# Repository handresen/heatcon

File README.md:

# HeatCon
Simple controller for water based floor heating.
The project was initiated when the old controller for the floor heating in our house broke down. I wanted the ability to control floor heating remotely from mobile and web. A prototype has been up and running for six weeks now without any problems.

## Summary
* Solid state switches (mosfets)
* Optocouplers to isolate MCU from 24V
* ESP8266 socket (WeMos D1 mini)
* Integrated switching power 24V-3.3V, single power for MCU and actuators
* No moving parts (ie no magnetic relays)
* EPS8266 powers opto couplers, mosfets drive the actuators
* Optionally separate ground and power for MCU and actuators
* Should work well for other actuators 6V-30V, up to 2.5A/channel (limited by PCB trace widths, more with thicker Cu)

## Schema

## Layout

## Model

## PCB
PCB by https://jlcpcb.com/, ENIG with black solder mask
<br/><br/>

<br/>

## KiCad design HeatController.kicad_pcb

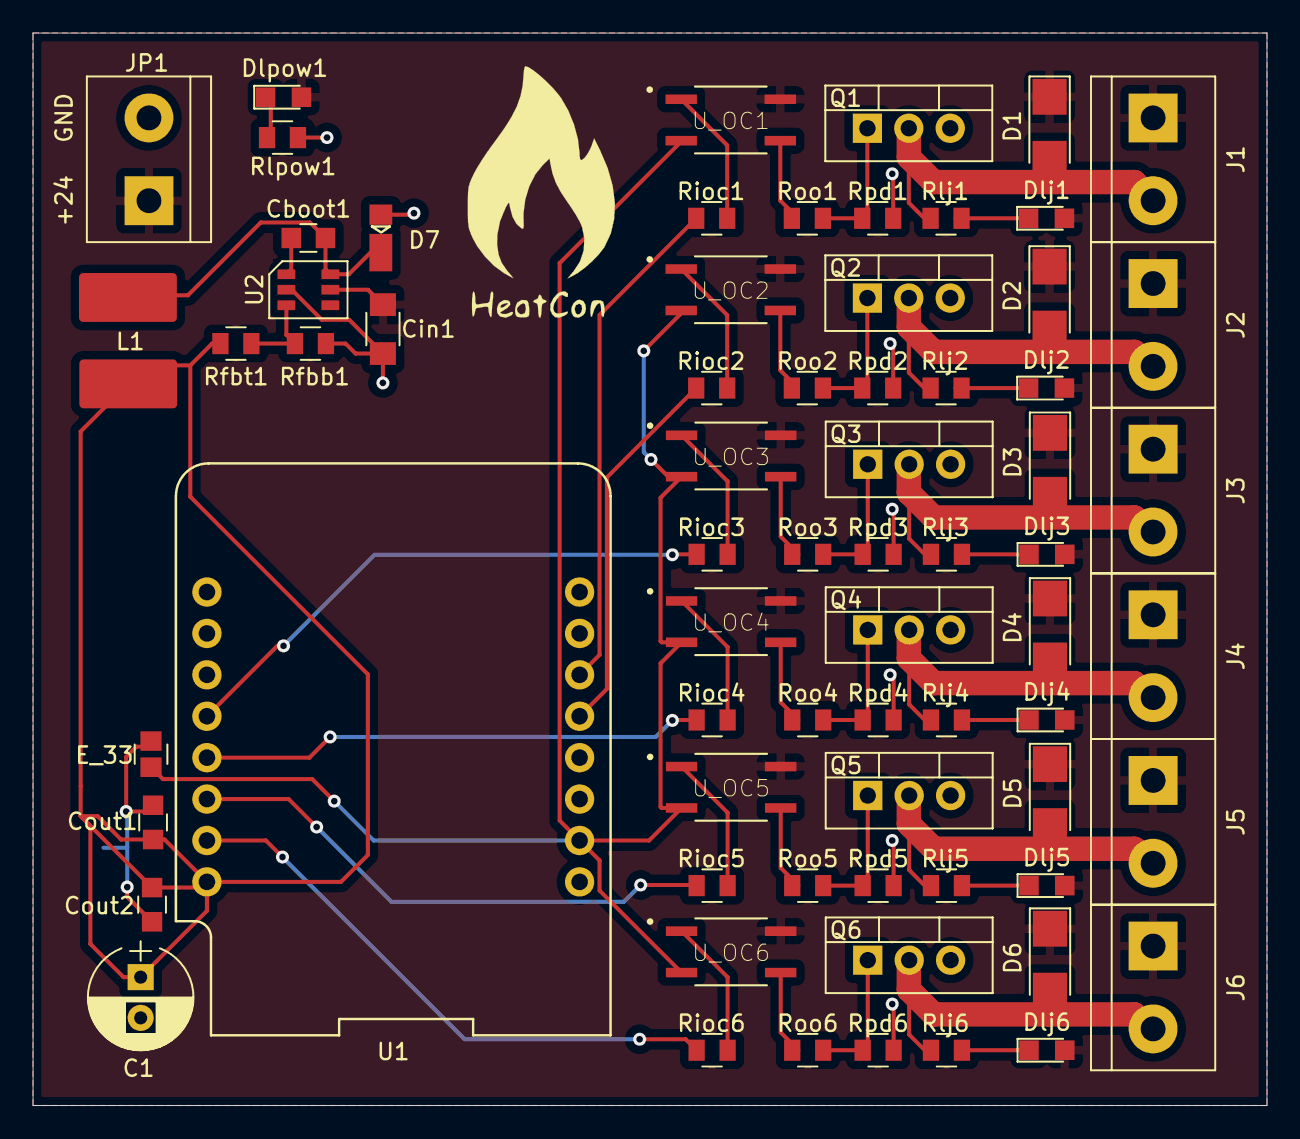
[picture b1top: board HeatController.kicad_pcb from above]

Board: 2 copper layers, 75.7 x 65.8 mm, 69 parts (0 on the bottom side), 44 nets.

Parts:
C1: 100uF; CP_Radial_D6.3mm_P2.50mm
Cboot1: 100nF; C_0805_H
Cin1: 4.7uF; C_1206
Cout1, Cout2: 22uF; C_0805_H
D1, D2, D3, D4, D5, D6: 1N4007; DO-214AC
D7: 600mV; SOD-123EP
Dlj1, Dlj2, Dlj3, Dlj4, Dlj5, Dlj6: LED; LED_0805
Dlpow1: LED; LED_0805
E_33: 0; R_0805_SHORT
J1, J2, J3, J4, J5, J6: Screw_Terminal_01x02; TerminalBlock_bornier-2_P5.08mm_tight
JP1: Screw_Terminal_01x02; TerminalBlock_bornier-2_P5.08mm_tight
L1: 15uH; SRN_INDUCTOR
Q1, Q2, Q3, Q4, Q5, Q6: IRF3205; TO-220-3_Vertical
Rfbb1: R; R_0805_H
Rfbt1: 64.9k; R_0805_H
Rioc1, Rioc2, Rioc3, Rioc4, Rioc5, Rioc6: 400; R_0805_H
Rlj1, Rlj2, Rlj3, Rlj4, Rlj5, Rlj6: 7k; R_0805_H
Rlpow1: 7k; R_0805_H
Roo1, Roo2, Roo3, Roo4, Roo5, Roo6: 20k; R_0805_H
Rpd1, Rpd2, Rpd3, Rpd4, Rpd5, Rpd6: 20k; R_0805_H
U1: WeMos_D1_mini; wemos-d1-mini-with-pin-header
U2: LMR14010ADDC; LRM14010A
U_OC1, U_OC2, U_OC3, U_OC4, U_OC5, U_OC6: EL357N(A)(TA)-G; SOP254P700X200-4N

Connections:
/3V3: C1.1, Cout1.1, Cout2.1, L1.1, Rfbt1.1, U1.8
/24V: Cin1.1, D1.1, D2.1, D3.1, D4.1, D5.1, D6.1, Dlj1.2, Dlj2.2, Dlj3.2, Dlj4.2, Dlj5.2, Dlj6.2, Dlpow1.2, J1.1, J2.1, J3.1, J4.1, J5.1, J6.1, JP1.1, U2.5, U_OC1.4, U_OC2.4, U_OC3.4, U_OC4.4, U_OC5.4, U_OC6.4
/D1: Rioc1.2, U1.14
/D2: Rioc2.2, U1.13
/D5: Rioc3.2, U1.4
/D6: Rioc4.2, U1.5
/D7: Rioc5.2, U1.6
/D8: Rioc6.2, U1.7
/GND2: E_33.1, U1.10, U_OC1.2, U_OC2.2, U_OC3.2, U_OC4.2, U_OC5.2, U_OC6.2
/SW: Cboot1.2, D7.1, L1.2, U2.6
GND: C1.2, Cin1.2, Cout1.2, Cout2.2, D7.2, E_33.2, JP1.2, Q1.3, Q2.3, Q3.3, Q4.3, Q5.3, Q6.3, Rfbb1.2, Rlpow1.1, Rpd1.2, Rpd2.2, Rpd3.2, Rpd4.2, Rpd5.2, Rpd6.2, U2.2
unnamed: Cboot1.1, U2.1
unnamed: D1.2, J1.2, Q1.2, Rlj1.2
unnamed: D2.2, J2.2, Q2.2, Rlj2.2
unnamed: D3.2, J3.2, Q3.2, Rlj3.2
unnamed: D4.2, J4.2, Q4.2, Rlj4.2
unnamed: D5.2, J5.2, Q5.2, Rlj5.2
unnamed: D6.2, J6.2, Q6.2, Rlj6.2
unnamed: Dlj1.1, Rlj1.1
unnamed: Dlj2.1, Rlj2.1
unnamed: Dlj3.1, Rlj3.1
unnamed: Dlj4.1, Rlj4.1
unnamed: Dlj5.1, Rlj5.1
unnamed: Dlj6.1, Rlj6.1
unnamed: Dlpow1.1, Rlpow1.2
unnamed: Q1.1, Roo1.2, Rpd1.1
unnamed: Q2.1, Roo2.2, Rpd2.1
unnamed: Q3.1, Roo3.2, Rpd3.1
unnamed: Q4.1, Roo4.2, Rpd4.1
unnamed: Q5.1, Roo5.2, Rpd5.1
unnamed: Q6.1, Roo6.2, Rpd6.1
unnamed: Rfbb1.1, Rfbt1.2, U2.3
unnamed: Rioc1.1, U_OC1.1
unnamed: Rioc2.1, U_OC2.1
unnamed: Rioc3.1, U_OC3.1
unnamed: Rioc4.1, U_OC4.1
unnamed: Rioc5.1, U_OC5.1
unnamed: Rioc6.1, U_OC6.1
unnamed: Roo1.1, U_OC1.3
unnamed: Roo2.1, U_OC2.3
unnamed: Roo3.1, U_OC3.3
unnamed: Roo4.1, U_OC4.3
unnamed: Roo5.1, U_OC5.3
unnamed: Roo6.1, U_OC6.3

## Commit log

2020-11-25 Initial commit w/files
2020-12-01 Added logo, thicker traces to terminals, gerbers
2022-02-16 backup lenovo
2025-12-17 added images
